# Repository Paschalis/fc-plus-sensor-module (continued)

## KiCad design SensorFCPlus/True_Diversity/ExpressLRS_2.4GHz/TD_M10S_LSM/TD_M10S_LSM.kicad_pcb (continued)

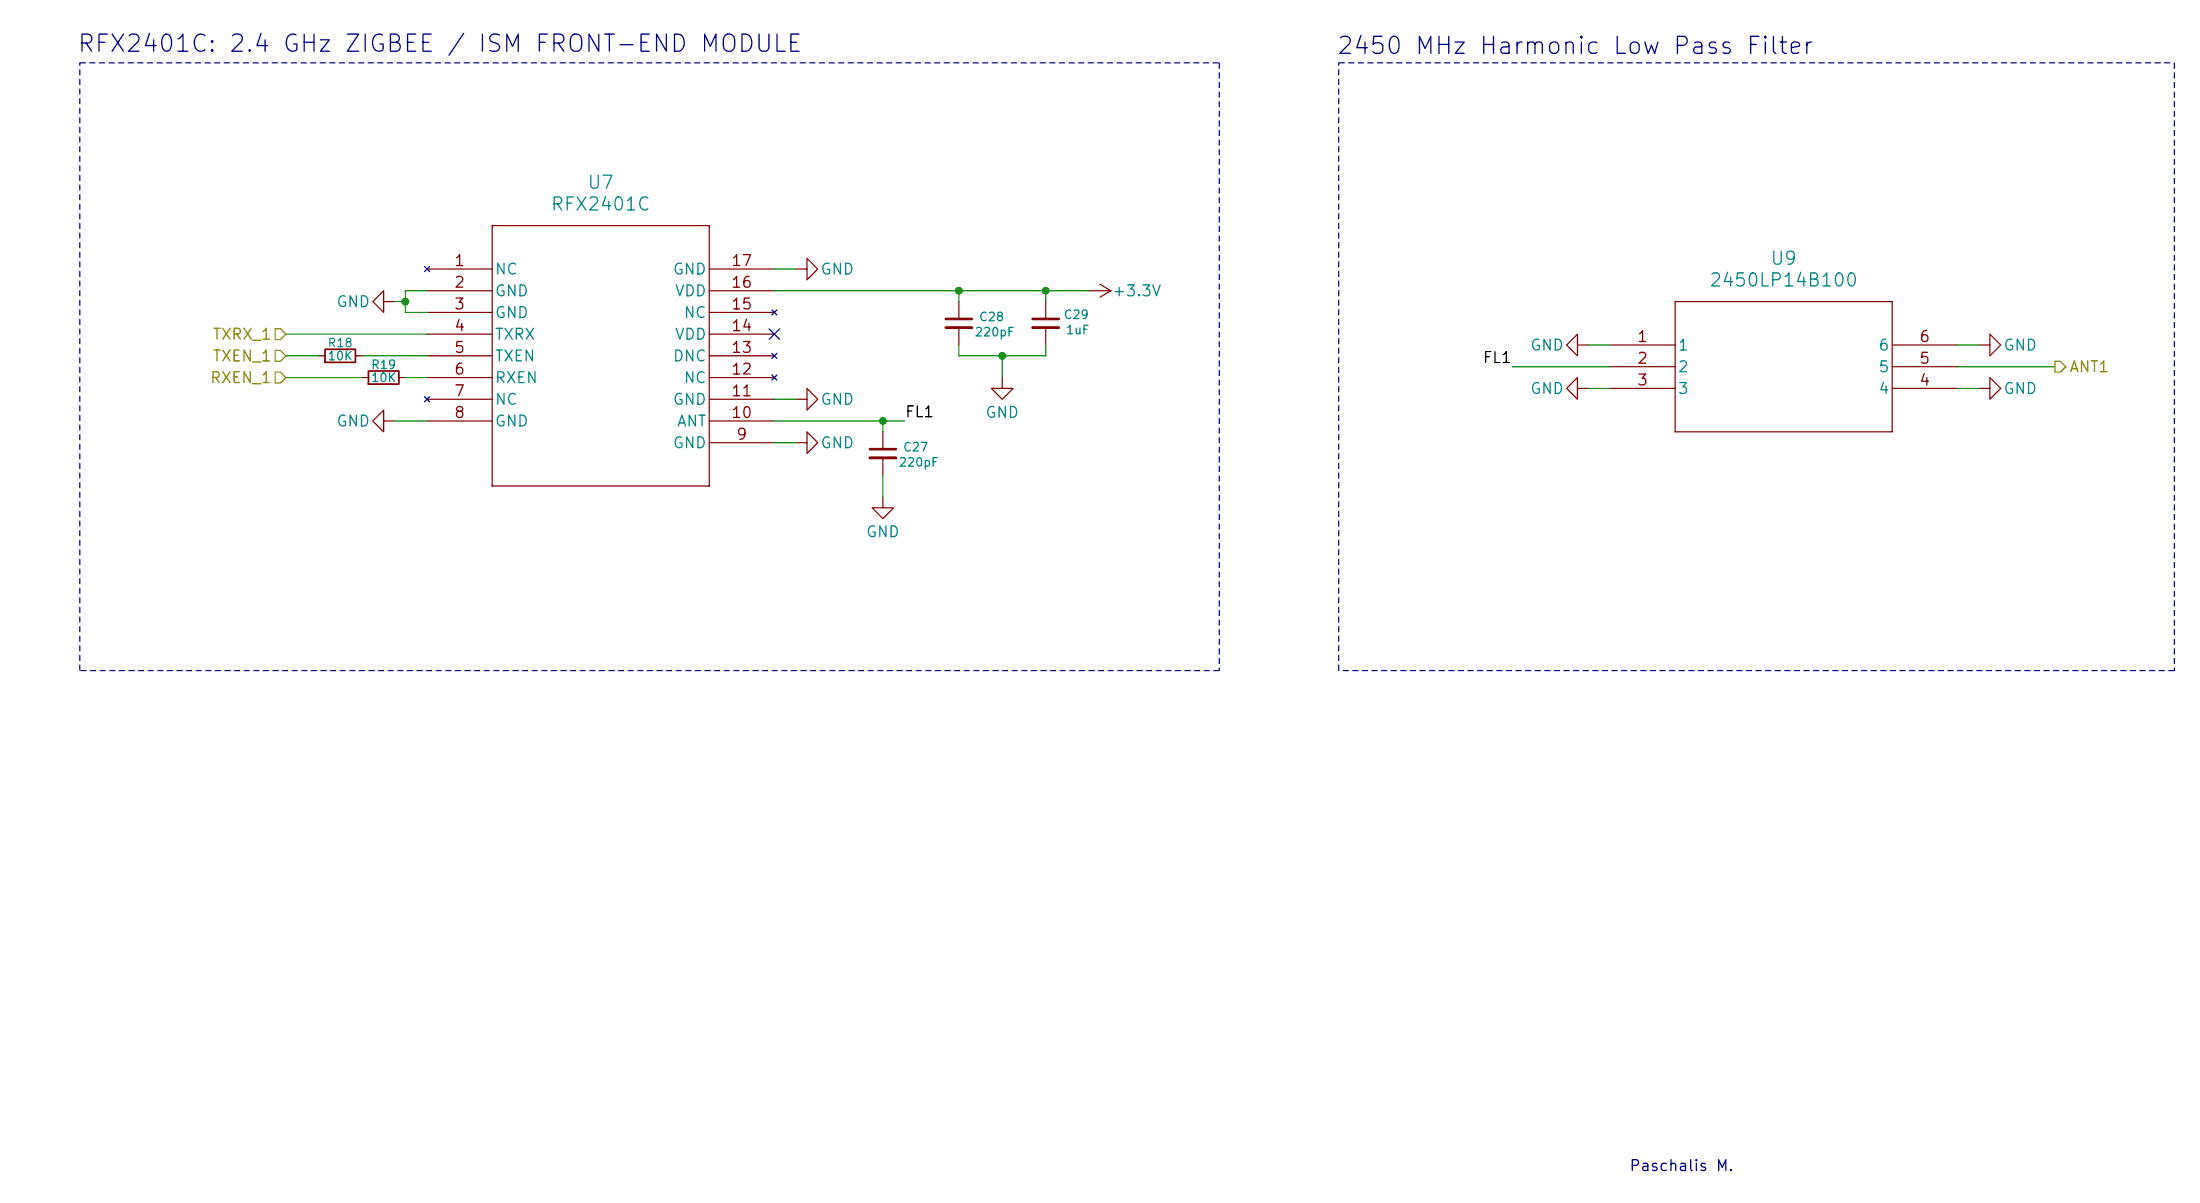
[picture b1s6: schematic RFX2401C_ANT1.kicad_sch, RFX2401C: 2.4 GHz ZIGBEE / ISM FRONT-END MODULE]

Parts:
C27, C28: 220pF; C_0603_1608Metric_Pad1.08x0.95mm_HandSolder
C29: 1uF; C_0603_1608Metric_Pad1.08x0.95mm_HandSolder
R18, R19: 10K; R_0603_1608Metric_Pad0.98x0.95mm_HandSolder
U7: RFX2401C; RFX2401C_SKY
U9: 2450LP14B100; CHIP_SMD_1P6XP8_JOD

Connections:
+3.3V: C28.1, C29.1, U7.16 (VDD); also elsewhere on the board
/ESP32/RXEN_1: R19.1; also elsewhere on the board
/ESP32/TXEN_1: R18.1; also elsewhere on the board
/RFX2401C_ANT1/ANT1: U9.5; also elsewhere on the board
/RFX2401C_ANT1/FL1: C27.1, U7.10 (ANT), U9.2
/RFX2401C_ANT1/TXRX_1: U7.4 (TXRX); also elsewhere on the board
GND: C27.2, C28.2, C29.2, U7.2 (GND), U7.3 (GND), U7.8 (GND), U7.9 (GND), U7.11 (GND), U7.17 (GND), U9.1, U9.3, U9.4, U9.6; also elsewhere on the board
unnamed: R19.2, U7.6 (RXEN)
unnamed: R18.2, U7.5 (TXEN)

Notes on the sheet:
2450 MHz Harmonic Low Pass Filter
Paschalis M.
RFX2401C: 2.4 GHz ZIGBEE / ISM FRONT-END MODULE

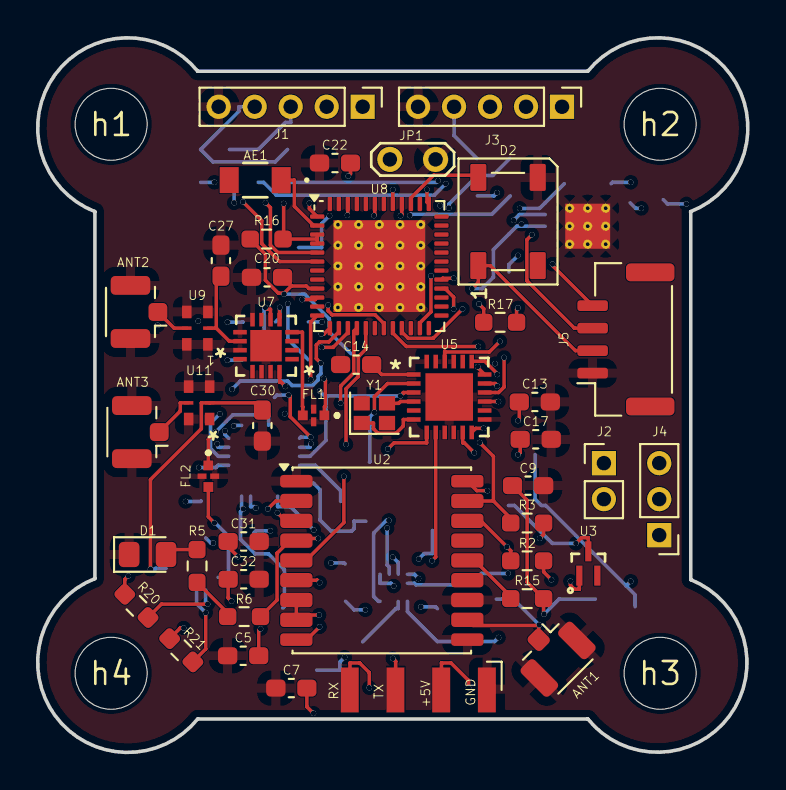
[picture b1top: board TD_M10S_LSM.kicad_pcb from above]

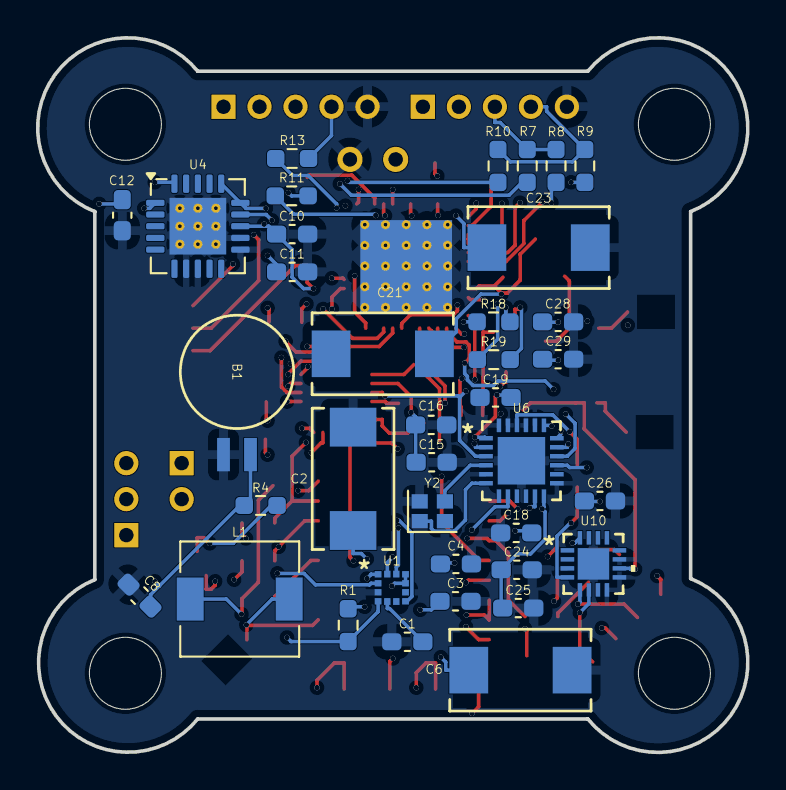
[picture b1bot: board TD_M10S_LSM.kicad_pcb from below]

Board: 4 copper layers, 39.4 x 39.7 mm, 85 parts (37 on the bottom side), 71 nets.

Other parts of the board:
h1, h2, h3, h4: MountingHole_4mm

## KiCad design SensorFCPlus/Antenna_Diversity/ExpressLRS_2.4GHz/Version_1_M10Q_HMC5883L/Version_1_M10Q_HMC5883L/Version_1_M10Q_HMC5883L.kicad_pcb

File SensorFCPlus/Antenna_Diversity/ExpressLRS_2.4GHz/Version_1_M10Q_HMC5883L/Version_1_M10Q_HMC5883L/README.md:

<div align="center">

# V1-M10Q-HMC

Antenna Diversity 
(GPS: SAM-M10Q, MAG: HMC5883L, ELRS:2.4GHz_RX)

</div>

## Bill of Materials

| Reference          | Value               | Datasheet                                                                 | Footprint                                                                                                      | Qty | DNP |
|--------------------|---------------------|---------------------------------------------------------------------------|---------------------------------------------------------------------------------------------------------------|-----|-----|
| AE1                | Antenna             | N/A                                                                       | RF_Antenna:Texas_SWRA117D_2.4GHz_Right                                                                        | 1   |     |
| ANT1, ANT2         | Conn_Coaxial        | N/A                                                                       | Connector_Coaxial:U.FL_Hirose_U.FL-R-SMT-1_Vertical                                                           | 2   |     |
| B1                 | MS621FEFL11E        | [Datasheet](MS621FEFL11E)                                                 | MS621FE-FL11E:MS621FE-FL11E                                                                                   | 1   |     |
| C1, C4, C6...      | 0.1uF               | N/A                                                                       | Capacitor_SMD:C_0805_2012Metric_Pad1.18x1.45mm_HandSolder                                                     | 6   |     |
| C2                 | 0.22uF              | N/A                                                                       | Capacitor_SMD:C_0805_2012Metric_Pad1.18x1.45mm_HandSolder                                                     | 1   |     |
| C3                 | 4.7uF               | N/A                                                                       | Capacitor_SMD:C_0805_2012Metric_Pad1.18x1.45mm_HandSolder                                                     | 1   |     |
| C5, C7, C14, C21   | 10uF                | N/A                                                                       | Capacitor_SMD:C_0805_2012Metric_Pad1.18x1.45mm_HandSolder, ECASD40J106M055K00:ECASD40J106M055K00              | 4   |     |
| C8                 | 1uF                 | N/A                                                                       | Capacitor_SMD:C_0805_2012Metric_Pad1.18x1.45mm_HandSolder                                                     | 1   |     |
| C9                 | 47uF                | N/A                                                                       | Capacitor_SMD:C_0805_2012Metric_Pad1.18x1.45mm_HandSolder                                                     | 1   |     |
| C10, C11, C16...   | 100nF               | N/A                                                                       | Capacitor_SMD:C_0805_2012Metric_Pad1.18x1.45mm_HandSolder                                                     | 10  |     |
| C22, C23, C30, C31 | 10pF                | N/A                                                                       | Capacitor_SMD:C_0805_2012Metric_Pad1.18x1.45mm_HandSolder                                                     | 4   |     |
| C25, C26           | 10nF                | N/A                                                                       | Capacitor_SMD:C_0805_2012Metric_Pad1.18x1.45mm_HandSolder                                                     | 2   |     |
| C27                | 470nF               | N/A                                                                       | Capacitor_SMD:C_0805_2012Metric_Pad1.18x1.45mm_HandSolder                                                     | 1   |     |
| C29                | 2.2uF               | N/A                                                                       | Capacitor_SMD:C_0805_2012Metric_Pad1.18x1.45mm_HandSolder                                                     | 1   |     |
| D1, D2             | LED                 | N/A                                                                       | LED_SMD:LED_0805_2012Metric_Pad1.15x1.40mm_HandSolder                                                         | 2   |     |
| FL1                | 2450FM07D0034T      | [Datasheet](https://www.mouser.co.uk/datasheet/2/611/2450FM07D0034-1375634.pdf) | 2450FM07D0034T:2450FM07D0034T                                                                                 | 1   |     |
| J1                 | Conn_01x05_Pin      | N/A                                                                       | Connector_PinHeader_2.00mm:PinHeader_1x05_P2.00mm_Vertical                                                    | 1   |     |
| J2                 | Conn_01x02_Pin      | N/A                                                                       | Connector_PinHeader_2.00mm:PinHeader_1x02_P2.00mm_Vertical                                                    | 1   |     |
| J3                 | Conn_01x03_Socket   | N/A                                                                       | Connector_JST:JST_GH_SM03B-GHS-TB_1x03-1MP_P1.25mm_Horizontal                                                 | 1   |     |
| J5                 | Conn_01x04_Pin      | N/A                                                                       | Connector_JST:JST_GH_SM04B-GHS-TB_1x04-1MP_P1.25mm_Horizontal                                                 | 1   |     |
| J6                 | Conn_01x04_Socket   | N/A                                                                       | Connector_Harwin:Harwin_M20-89004xx_1x04_P2.54mm_Horizontal                                                   | 1   |     |
| JP1                | Jumper_2_Bridged    | N/A                                                                       | Jumper:SolderJumper-2_P1.3mm_Open_RoundedPad1.0x1.5mm                                                         | 1   |     |
| R1, R2, R8, R9     | 1.5K                | N/A                                                                       | Resistor_SMD:R_0805_2012Metric_Pad1.20x1.40mm_HandSolder                                                      | 4   |     |
| R3, R6, R18...     | 0                   | N/A                                                                       | Resistor_SMD:R_0603_1608Metric_Pad0.98x0.95mm_HandSolder, Resistor_SMD:R_0805_2012Metric_Pad1.20x1.40mm_HandSolder | 8   |     |
| R4                 | 4.7K                | N/A                                                                       | Resistor_SMD:R_0805_2012Metric_Pad1.20x1.40mm_HandSolder                                                      | 1   |     |
| R5, R7             | 1K                  | N/A                                                                       | Resistor_SMD:R_0805_2012Metric_Pad1.20x1.40mm_HandSolder                                                      | 2   |     |
| R10, R11, R12...   | 10K                 | N/A                                                                       | Resistor_SMD:R_0805_2012Metric_Pad1.20x1.40mm_HandSolder                                                      | 5   |     |
| R14                | 12K                 | N/A                                                                       | Resistor_SMD:R_0805_2012Metric_Pad1.20x1.40mm_HandSolder                                                      | 1   |     |
| R15                | 2.2K                | N/A                                                                       | Resistor_SMD:R_0805_2012Metric_Pad1.20x1.40mm_HandSolder                                                      | 1   |     |
| R16                | 1.2K                | N/A                                                                       | Resistor_SMD:R_0805_2012Metric_Pad1.20x1.40mm_HandSolder                                                      | 1   |     |
| U1                 | HMC5883L            | [Datasheet](HMC5883L)                                                     | HMC5883L:LPCC16_HNW                                                                                           | 1   |     |
| U2                 | SAM-M10Q-00B        | [Datasheet](SAM-M10Q-00B)                                                 | SAM-M10Q-00B:SAM-M10Q_UBL                                                                                     | 1   |     |
| U3                 | BAT54STA            | [Datasheet](BAT54STA)                                                     | BAT54STA:BAT54STA                                                                                             | 1   |     |
| U4                 | TPS7A4701xRGW       | [Datasheet](https://www.ti.com/lit/ds/symlink/tps7a47.pdf)               | Package_DFN_QFN:Texas_RGW0020A_VQFN-20-1EP_5x5mm_P0.65mm_EP3.15x3.15mm_ThermalVias                            | 1   |     |
| U5                 | ESP8285H16          | [Datasheet](ESP8285H16)                                                   | ESP8285H16:QFN32_5X5_EXP                                                                                      | 1   |     |
| U6                 | SX1280IMLTRT       | [Datasheet](SX1280IMLTRT)                                                | SX1280IMLTRT:QFN24_4X4_SEM                                                                                    | 1   |     |
| U7                 | SE2431L-R           | [Datasheet](SE2431L-R)                                                    | SE2431L-R:SE2431L_SKY                                                                                         | 1   |     |
| Y1                 | 26MHz               | N/A                                                                       | Crystal:Crystal_SMD_2016-4Pin_2.0x1.6mm                                                                       | 1   |     |
| Y2                 | 52MHz               | N/A                                                                       | Crystal:Crystal_SMD_2016-4Pin_2.0x1.6mm                                                                       | 1   |     |

[⬅️ Go Back to Main README](https://github.com/Paschalis/fc-plus-sensor-module)

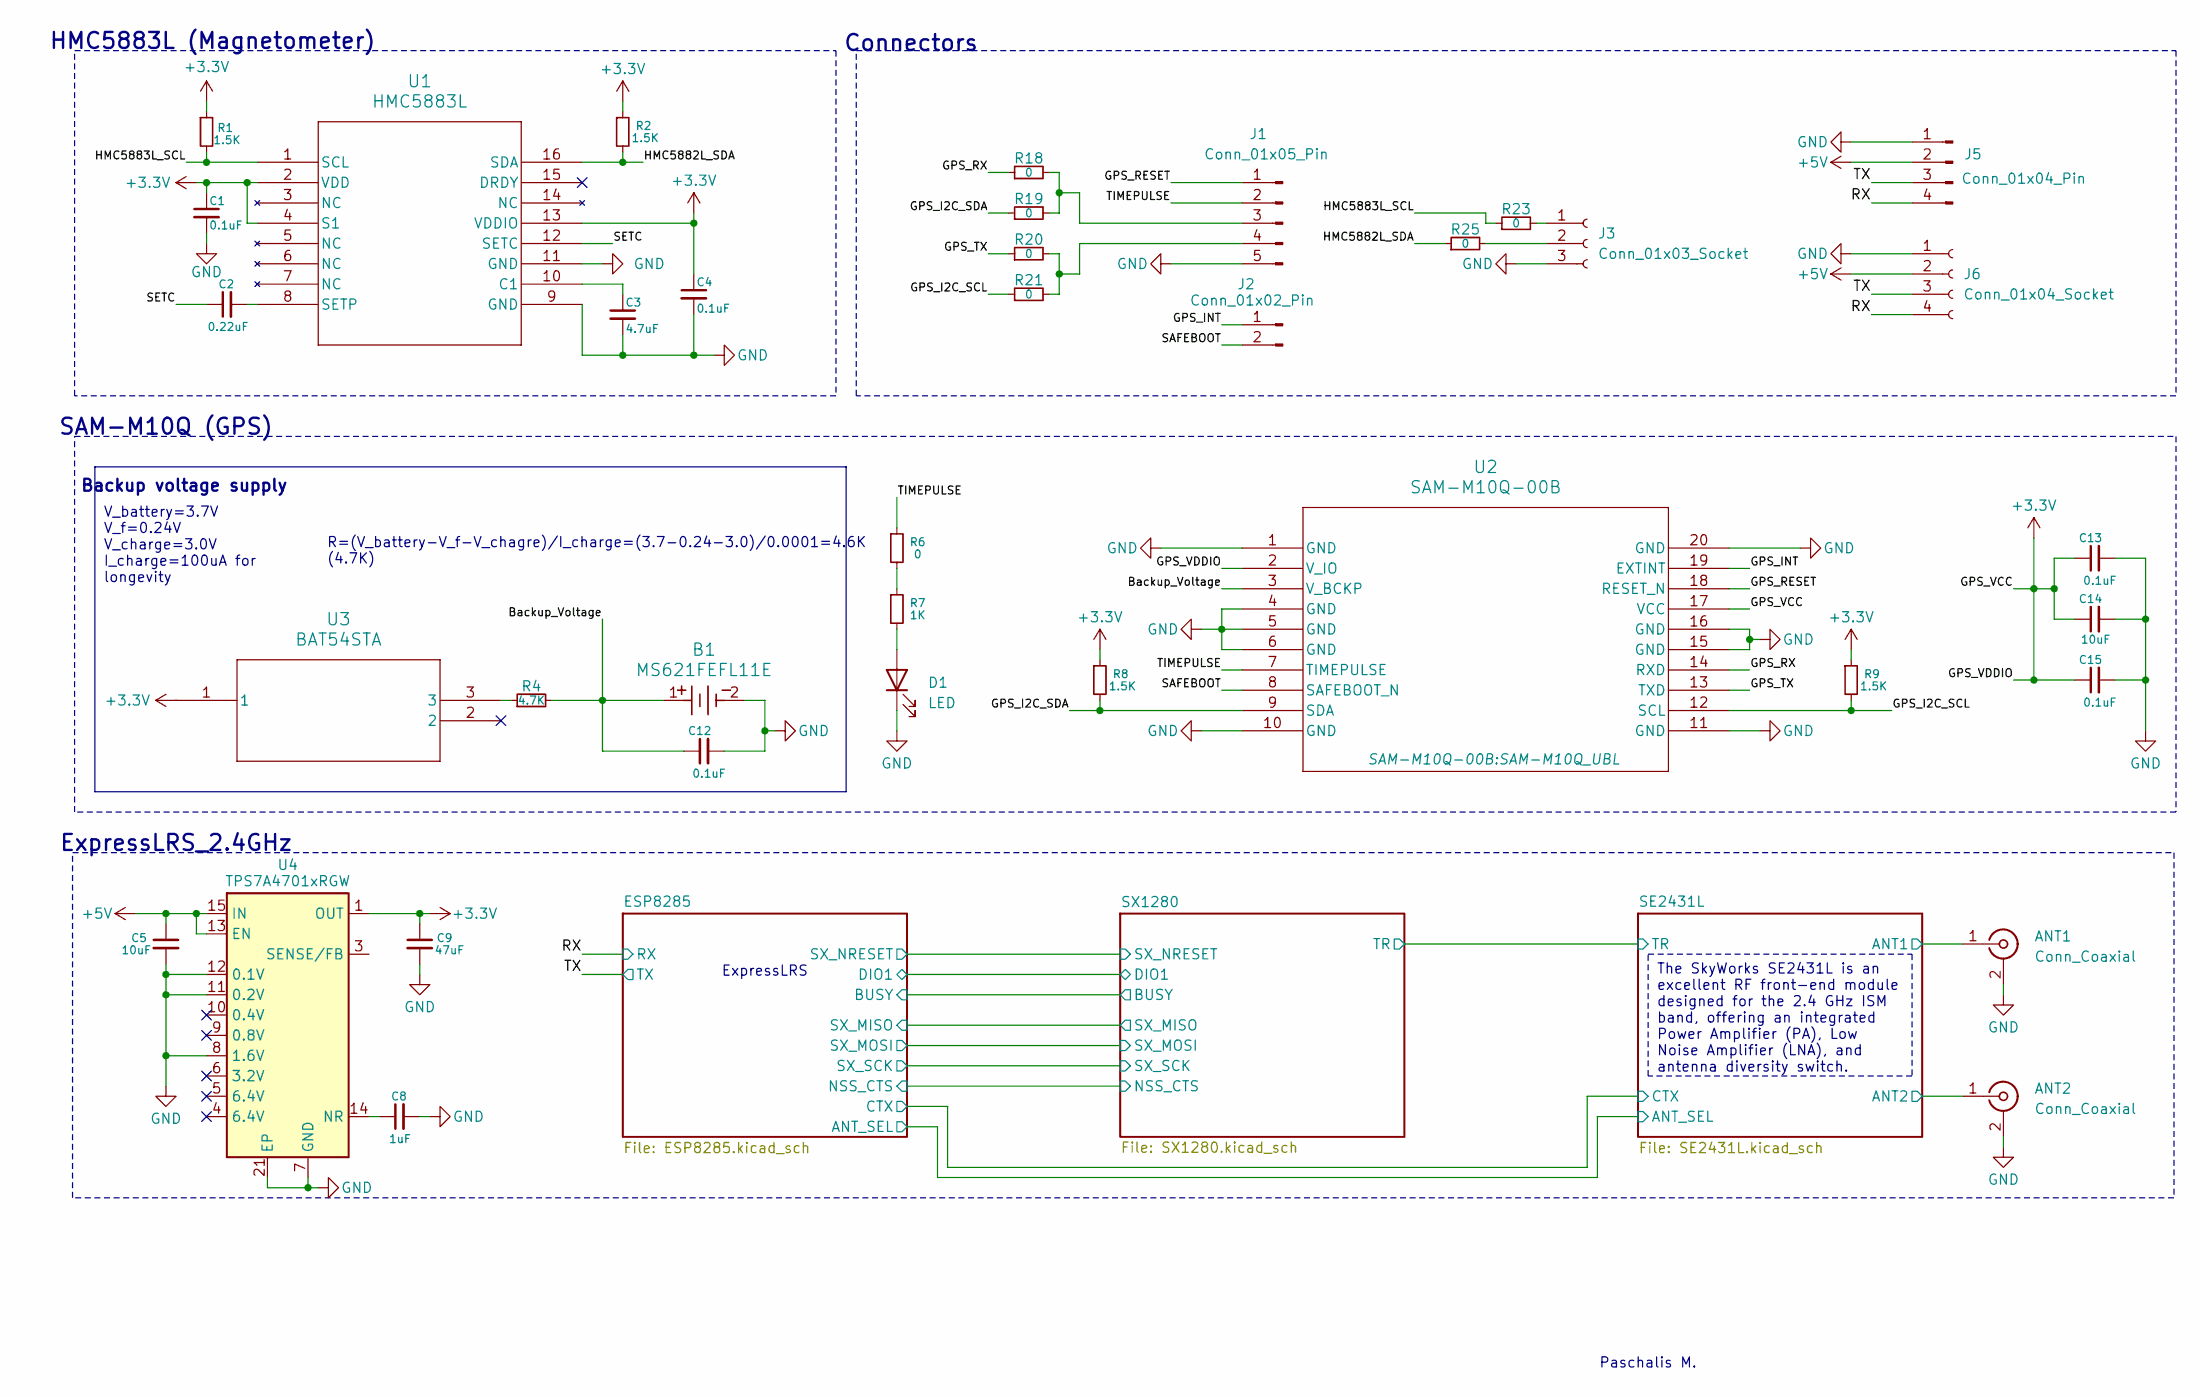
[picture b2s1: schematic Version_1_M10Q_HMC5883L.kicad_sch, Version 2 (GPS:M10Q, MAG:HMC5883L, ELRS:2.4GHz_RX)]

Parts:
ANT1, ANT2: Conn_Coaxial; U.FL_Hirose_U.FL-R-SMT-1_Vertical
B1: MS621FEFL11E; MS621FE-FL11E
C1, C4, C12, C13, C15: 0.1uF; C_0805_2012Metric_Pad1.18x1.45mm_HandSolder
C2: 0.22uF; C_0805_2012Metric_Pad1.18x1.45mm_HandSolder
C3: 4.7uF; C_0805_2012Metric_Pad1.18x1.45mm_HandSolder
C5: 10uF; C_0805_2012Metric_Pad1.18x1.45mm_HandSolder
C8: 1uF; C_0805_2012Metric_Pad1.18x1.45mm_HandSolder
C9: 47uF; C_0805_2012Metric_Pad1.18x1.45mm_HandSolder
C14: 10uF; ECASD40J106M055K00
D1: LED; LED_0805_2012Metric_Pad1.15x1.40mm_HandSolder
J1: Conn_01x05_Pin; PinHeader_1x05_P2.00mm_Vertical
J2: Conn_01x02_Pin; PinHeader_1x02_P2.00mm_Vertical
J3: Conn_01x03_Socket; JST_GH_SM03B-GHS-TB_1x03-1MP_P1.25mm_Horizontal
J5: Conn_01x04_Pin; JST_GH_SM04B-GHS-TB_1x04-1MP_P1.25mm_Horizontal
J6: Conn_01x04_Socket; Harwin_M20-89004xx_1x04_P2.54mm_Horizontal
R1, R2, R8, R9: 1.5K; R_0805_2012Metric_Pad1.20x1.40mm_HandSolder
R4: 4.7K; R_0805_2012Metric_Pad1.20x1.40mm_HandSolder
R6: 0; R_0805_2012Metric_Pad1.20x1.40mm_HandSolder
R7: 1K; R_0805_2012Metric_Pad1.20x1.40mm_HandSolder
R18, R19, R20, R21, R23, R25: 0; R_0603_1608Metric_Pad0.98x0.95mm_HandSolder
U1: HMC5883L; LPCC16_HNW
U2: SAM-M10Q-00B; SAM-M10Q_UBL
U3: BAT54STA
U4: TPS7A4701xRGW; Texas_RGW0020A_VQFN-20-1EP_5x5mm_P0.65mm_EP3.15x3.15mm_Ther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

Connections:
+3.3V: C1.1, C4.1, C9.1, C13.1, C14.1, C15.1, R1.1, R2.1, R8.1, R9.1, U1.2 (VDD), U1.4 (S1), U1.13 (VDDIO), U2.2 (V_IO), U2.17 (VCC), U3.1, U4.1 (OUT), U4.20 (OUT); also elsewhere on the board
+5V: C5.1, J5.2, J6.2, U4.13 (EN), U4.15 (IN), U4.16 (IN)
/Backup_Voltage: B1.1, C12.1, R4.2, U2.3 (V_BCKP)
/GPS_I2C_SCL: R9.2, R21.1, U2.12 (SCL)
/GPS_I2C_SDA: R8.2, R19.1, U2.9 (SDA)
/GPS_INT: J2.1, U2.19 (EXTINT)
/GPS_RESET: J1.1, U2.18 (RESET_N)
/GPS_RX: R18.1, U2.14 (RXD)
/GPS_TX: R20.1, U2.13 (TXD)
/HMC5882L_SDA: R2.2, R25.1, U1.16 (SDA)
/HMC5883L_SCL: R1.2, R23.1, U1.1 (SCL)
/RX: J5.4, J6.4; also elsewhere on the board
/SAFEBOOT: J2.2, U2.8 (SAFEBOOT_N)
/SE2431L/ANT1: ANT1.1 (In); also elsewhere on the board
/SE2431L/ANT2: ANT2.1 (In); also elsewhere on the board
/SETC: C2.1, U1.12 (SETC)
/TIMEPULSE: J1.2, R6.1, U2.7 (TIMEPULSE)
/TX: J5.3, J6.3; also elsewhere on the board
GND: ANT1.2 (Ext), ANT2.2 (Ext), B1.2, C1.2, C3.2, C4.2, C5.2, C8.2, C9.2, C12.2, C13.2, C14.2, C15.2, D1.1 (K), J1.5, J3.3, J5.1, J6.1, U1.9 (GND), U1.11 (GND), U2.1 (GND), U2.4 (GND), U2.5 (GND), U2.6 (GND), U2.10 (GND), U2.11 (GND), U2.15 (GND), U2.16 (GND), U2.20 (GND), U4.7 (GND), U4.8 (1.6V), U4.11 (0.2V), U4.12 (0.1V), U4.21 (EP); also elsewhere on the board
unnamed: D1.2 (A), R7.2
unnamed: J1.3, R18.2, R19.2
unnamed: J1.4, R20.2, R21.2
unnamed: J3.1, R23.2
unnamed: J3.2, R25.2
unnamed: R4.1, U3.3
unnamed: R6.2, R7.1
unnamed: C3.1, U1.10 (C1)
unnamed: C2.2, U1.8 (SETP)
unnamed: C8.1, U4.14 (NR)

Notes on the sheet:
The SkyWorks SE2431L is an excellent RF front-end module designed for the 2.4 GHz ISM band, offering an integrated Power Amplifier (PA), Low Noise Amplifier (LNA), and antenna diversity switch.
R=(V_battery-V_f-V_chagre)/I_charge=(3.7-0.24-3.0)/0.0001=4.6K (4.7K)
V_battery=3.7V V_f=0.24V V_charge=3.0V I_charge=100uA for longevity
HMC5883L (Magnetometer)
ExpressLRS
Connectors
ExpressLRS_2.4GHz
Backup voltage supply
SAM-M10Q (GPS)
Paschalis M.

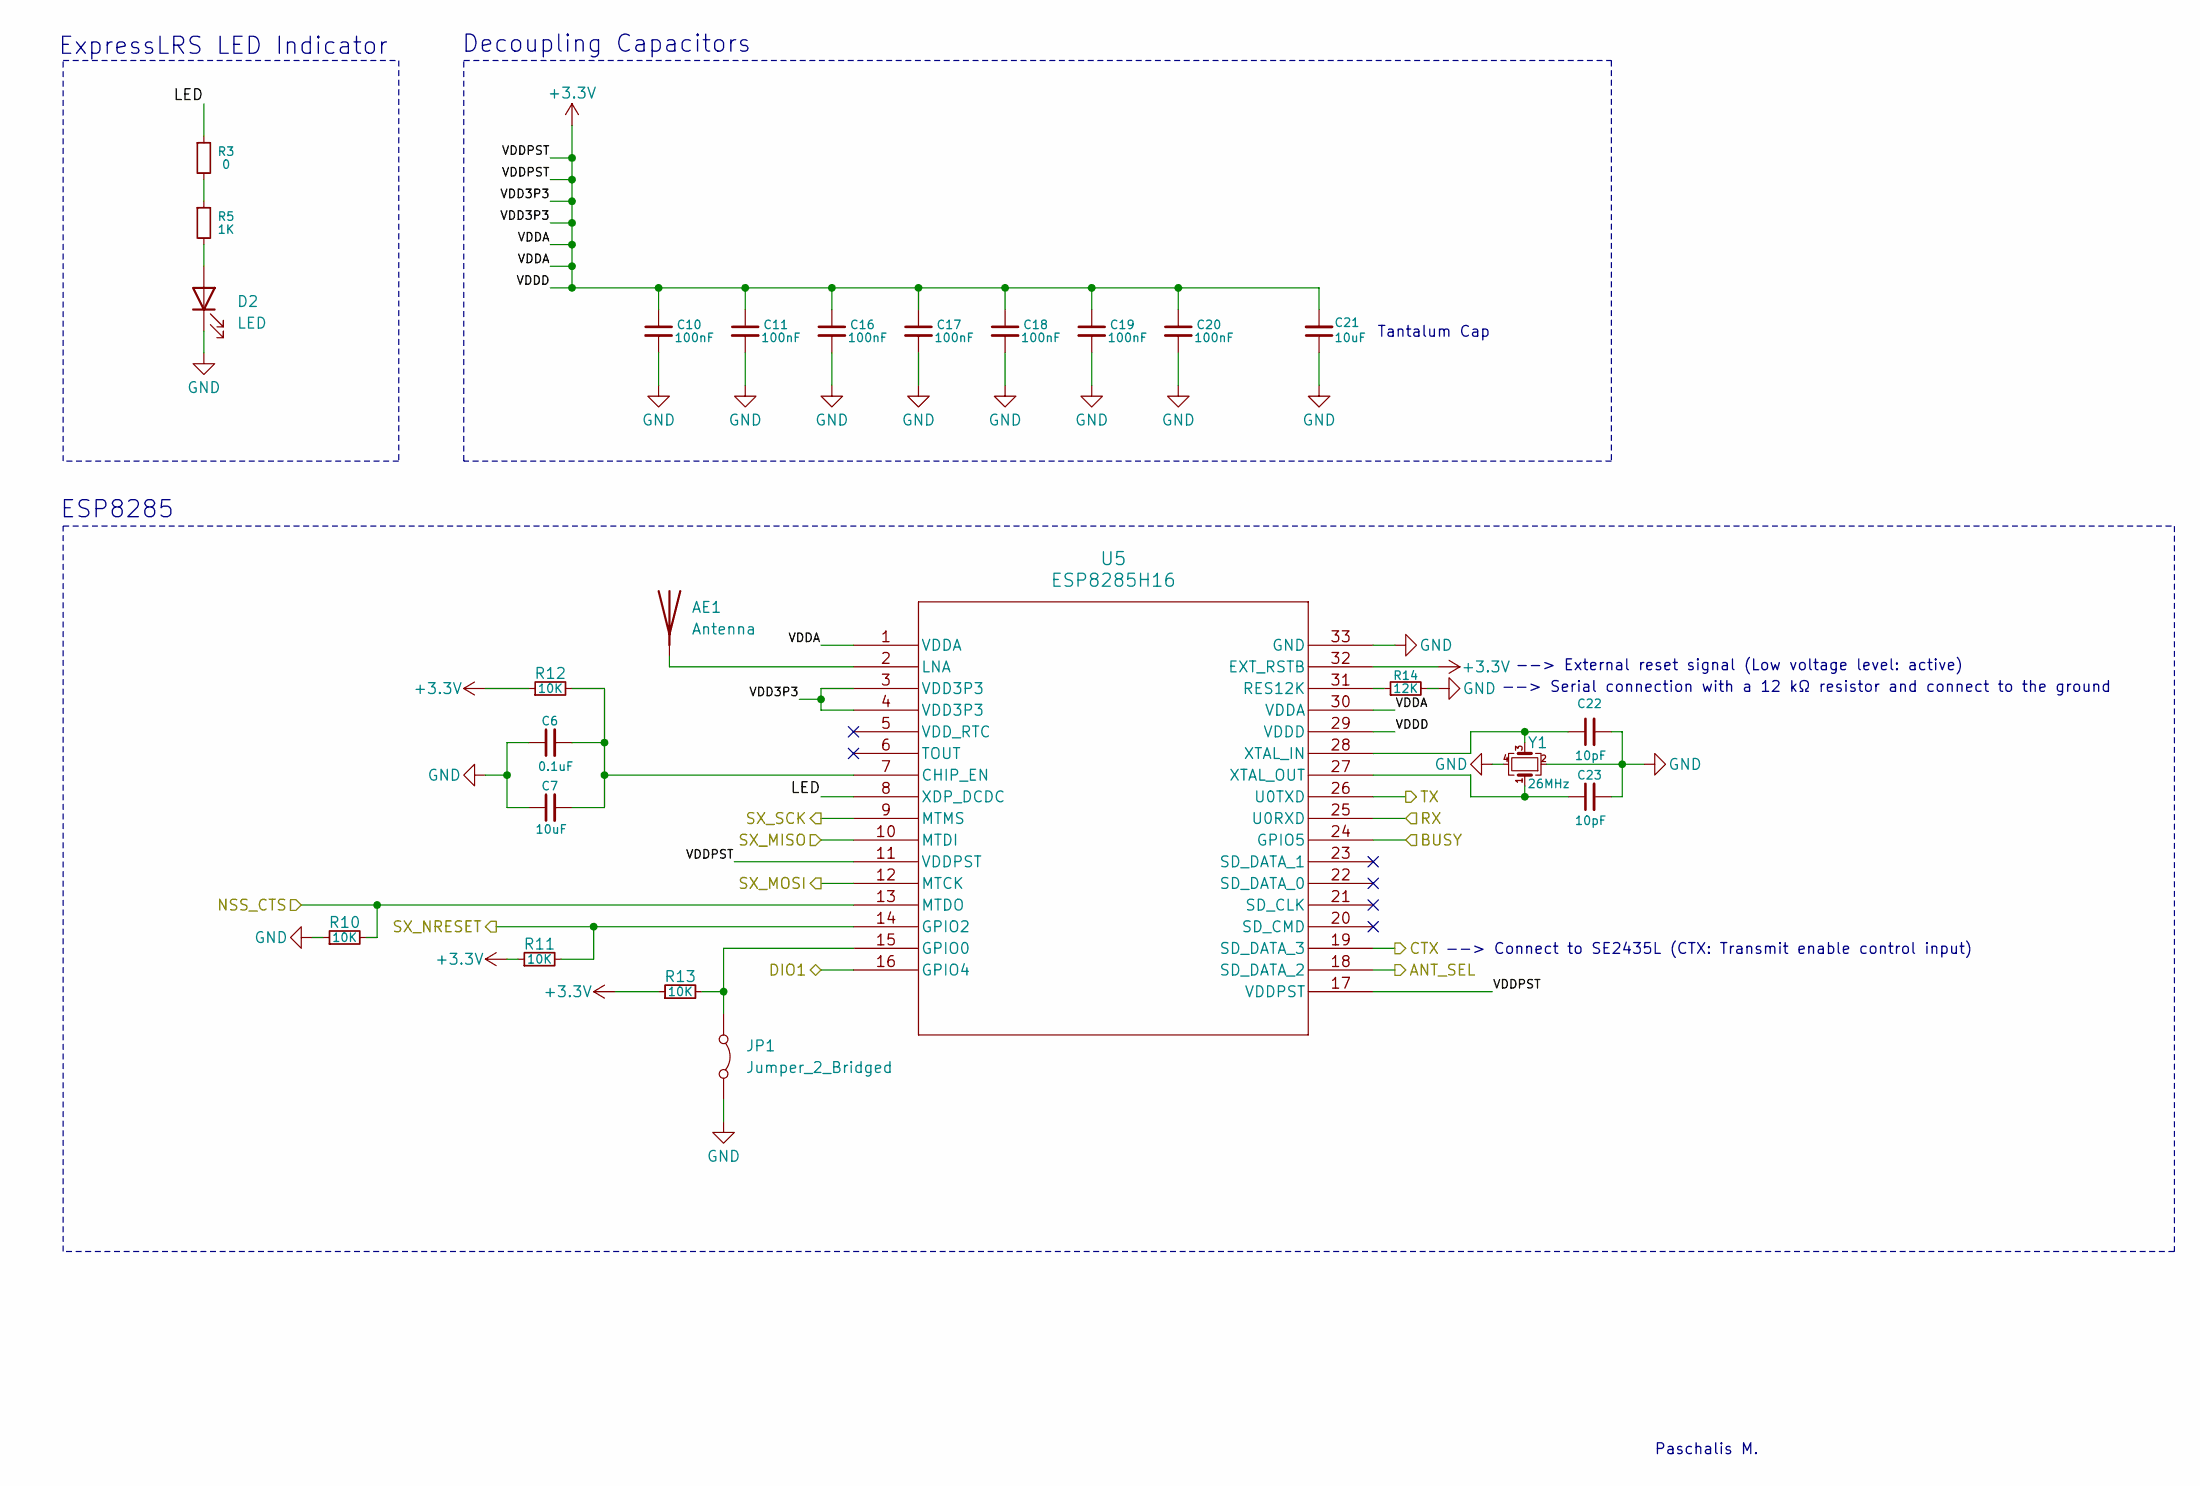
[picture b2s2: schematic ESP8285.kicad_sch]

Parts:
AE1: Antenna; Texas_SWRA117D_2.4GHz_Right
C6: 0.1uF; C_0805_2012Metric_Pad1.18x1.45mm_HandSolder
C7, C21: 10uF; ECASD40J106M055K00
C10, C11, C16, C17, C18, C19, C20: 100nF; C_0805_2012Metric_Pad1.18x1.45mm_HandSolder
C22, C23: 10pF; C_0805_2012Metric_Pad1.18x1.45mm_HandSolder
D2: LED; LED_0805_2012Metric_Pad1.15x1.40mm_HandSolder
JP1: Jumper_2_Bridged; SolderJumper-2_P1.3mm_Open_RoundedPad1.0x1.5mm
R3: 0; R_0805_2012Metric_Pad1.20x1.40mm_HandSolder
R5: 1K; R_0805_2012Metric_Pad1.20x1.40mm_HandSolder
R10, R11, R12, R13: 10K; R_0805_2012Metric_Pad1.20x1.40mm_HandSolder
R14: 12K; R_0805_2012Metric_Pad1.20x1.40mm_HandSolder
U5: ESP8285H16; QFN32_5X5_EXP
Y1: 26MHz; Crystal_SMD_2016-4Pin_2.0x1.6mm

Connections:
+3.3V: C10.1, C11.1, C16.1, C17.1, C18.1, C19.1, C20.1, C21.2, R11.1, R12.1, R13.1, U5.1 (VDDA), U5.3 (VDD3P3), U5.4 (VDD3P3), U5.11 (VDDPST), U5.17 (VDDPST), U5.29 (VDDD), U5.30 (VDDA), U5.32 (EXT_RSTB); also elsewhere on the board
/ESP8285/ANT_SEL: U5.18 (SD_DATA_2); also elsewhere on the board
/ESP8285/BUSY: U5.24 (GPIO5); also elsewhere on the board
/ESP8285/CTX: U5.19 (SD_DATA_3); also elsewhere on the board
/ESP8285/DIO1: U5.16 (GPIO4); also elsewhere on the board
/ESP8285/LED: R3.1, U5.8 (XDP_DCDC)
/ESP8285/NSS_CTS: R10.2, U5.13 (MTDO); also elsewhere on the board
/ESP8285/SX_MISO: U5.10 (MTDI); also elsewhere on the board
/ESP8285/SX_MOSI: U5.12 (MTCK); also elsewhere on the board
/ESP8285/SX_NRESET: R11.2, U5.14 (GPIO2); also elsewhere on the board
/ESP8285/SX_SCK: U5.9 (MTMS); also elsewhere on the board
/RX: U5.25 (U0RXD); also elsewhere on the board
/TX: U5.26 (U0TXD); also elsewhere on the board
GND: C6.1, C7.1, C10.2, C11.2, C16.2, C17.2, C18.2, C19.2, C20.2, C21.1, C22.2, C23.2, D2.1 (K), JP1.2 (B), R10.1, R14.2, U5.33 (GND), Y1.2, Y1.4; also elsewhere on the board
unnamed: AE1.1, U5.2 (LNA)
unnamed: D2.2 (A), R5.2
unnamed: JP1.1 (A), R13.2, U5.15 (GPIO0)
unnamed: R3.2, R5.1
unnamed: C6.2, C7.2, R12.2, U5.7 (CHIP_EN)
unnamed: R14.1, U5.31 (RES12K)
unnamed: C22.1, U5.28 (XTAL_IN), Y1.3
unnamed: C23.1, U5.27 (XTAL_OUT), Y1.1

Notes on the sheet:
ESP8285
Paschalis M.
Decoupling Capacitors
--> Serial connection with a 12 kΩ resistor and connect to the ground
--> Connect to SE2435L (CTX: Transmit enable control input)
--> External reset signal (Low voltage level: active)
ExpressLRS LED Indicator
Tantalum Cap

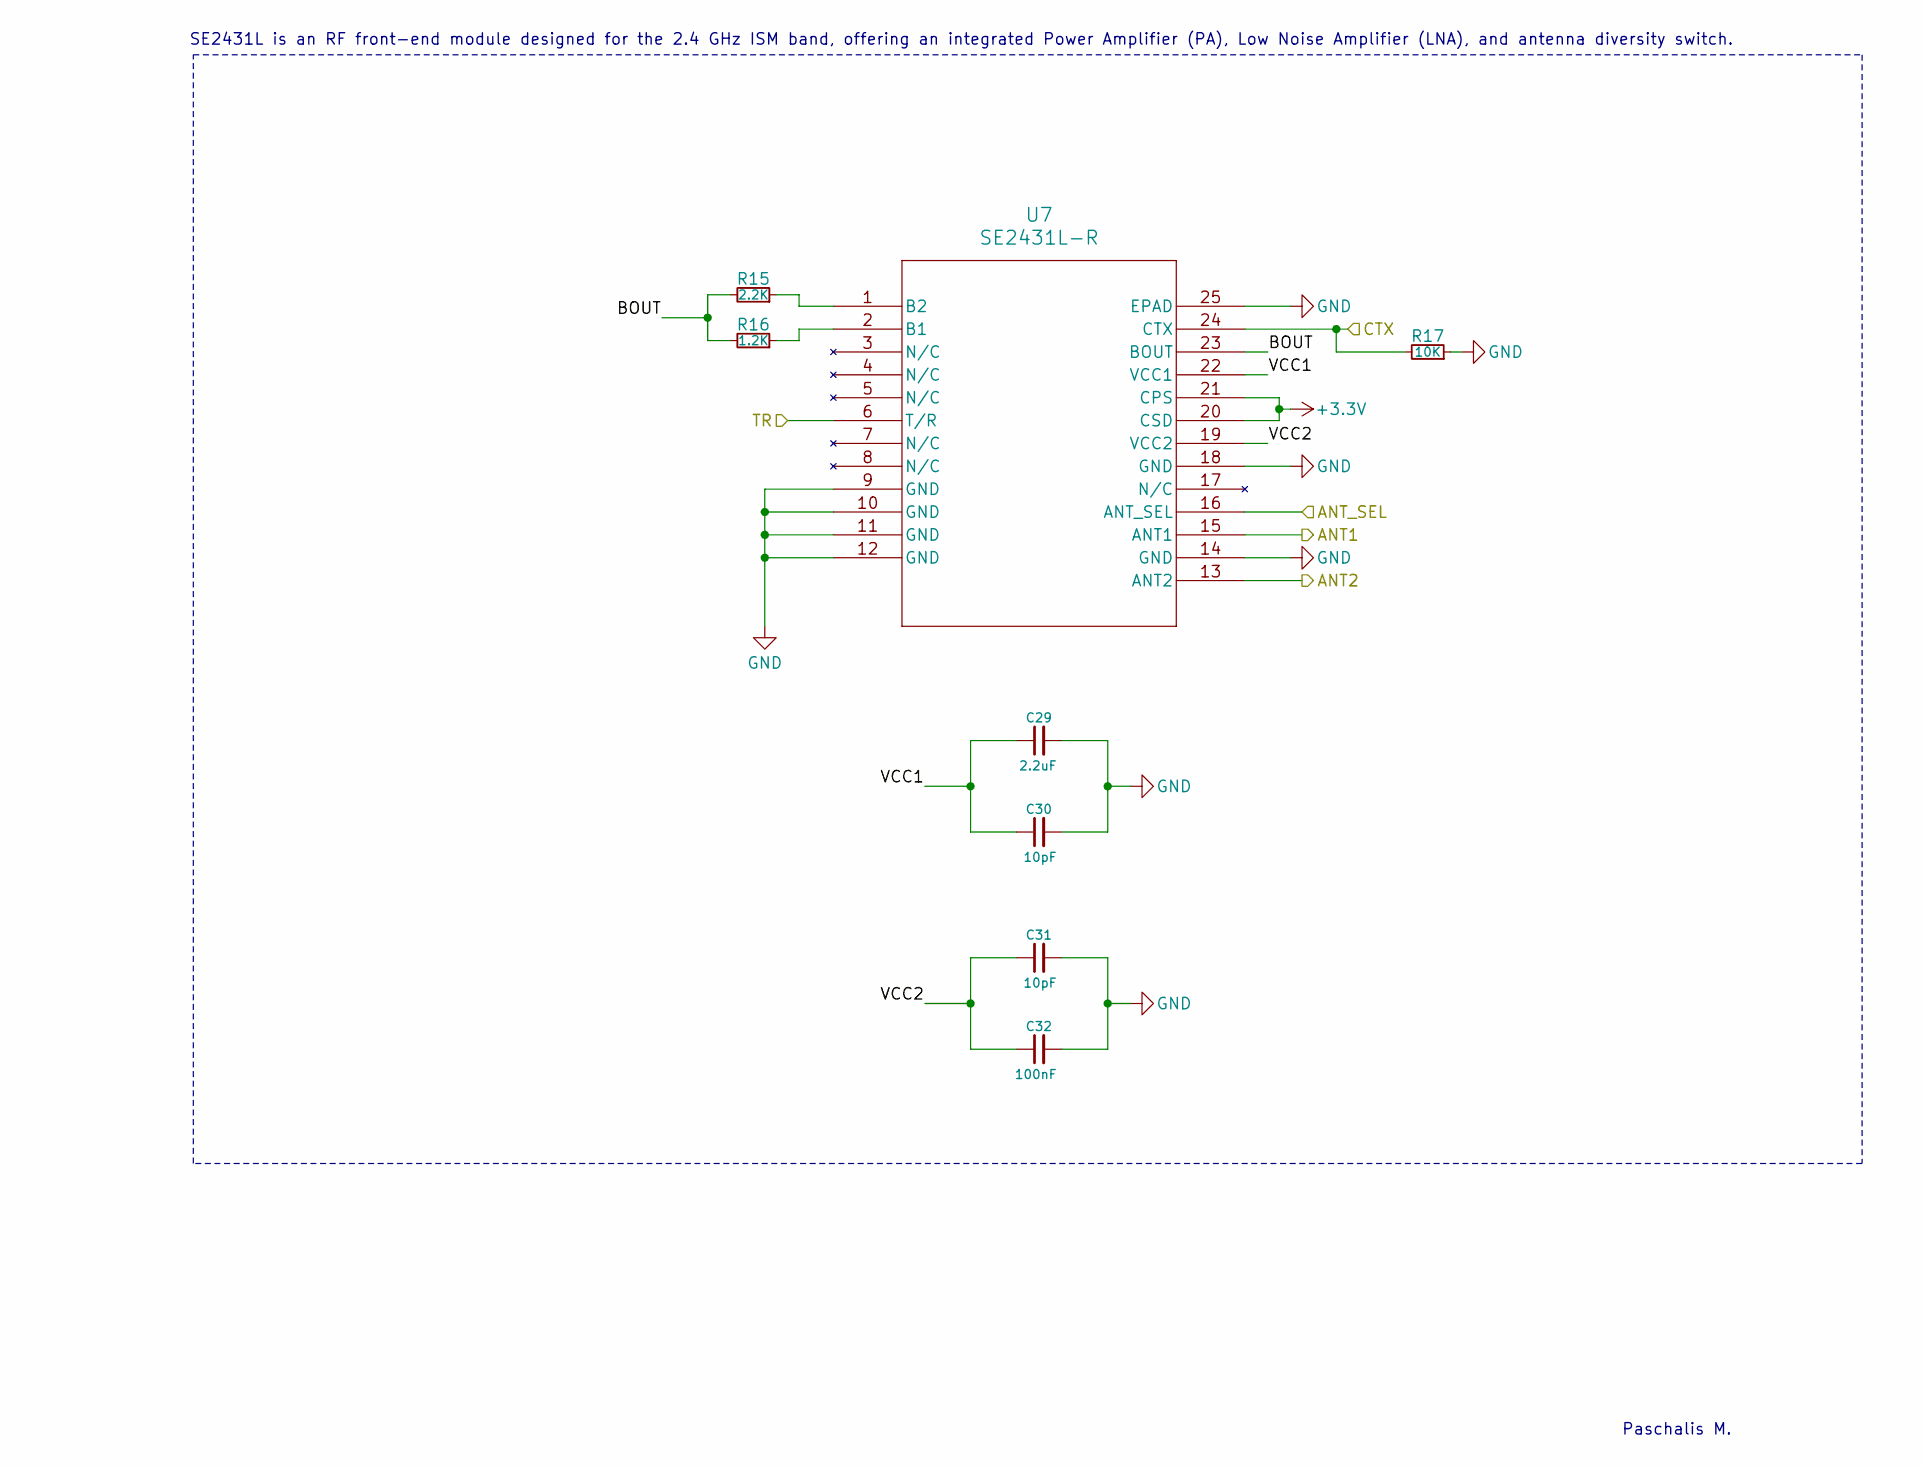
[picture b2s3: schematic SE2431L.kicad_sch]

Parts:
C29: 2.2uF; C_0805_2012Metric_Pad1.18x1.45mm_HandSolder
C30, C31: 10pF; C_0805_2012Metric_Pad1.18x1.45mm_HandSolder
C32: 100nF; C_0805_2012Metric_Pad1.18x1.45mm_HandSolder
R15: 2.2K; R_0805_2012Metric_Pad1.20x1.40mm_HandSolder
R16: 1.2K; R_0805_2012Metric_Pad1.20x1.40mm_HandSolder
R17: 10K; R_0805_2012Metric_Pad1.20x1.40mm_HandSolder
U7: SE2431L-R; SE2431L_SKY

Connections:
+3.3V: U7.20 (CSD), U7.21 (CPS); also elsewhere on the board
/ESP8285/ANT_SEL: U7.16 (ANT_SEL); also elsewhere on the board
/ESP8285/CTX: R17.2, U7.24 (CTX); also elsewhere on the board
/SE2431L/ANT1: U7.15 (ANT1); also elsewhere on the board
/SE2431L/ANT2: U7.13 (ANT2); also elsewhere on the board
/SE2431L/BOUT: R15.2, R16.2, U7.23 (BOUT)
/SE2431L/TR: U7.6 (T/R); also elsewhere on the board
/SE2431L/VCC1: C29.1, C30.1, U7.22 (VCC1)
/SE2431L/VCC2: C31.1, C32.1, U7.19 (VCC2)
GND: C29.2, C30.2, C31.2, C32.2, R17.1, U7.9 (GND), U7.10 (GND), U7.11 (GND), U7.12 (GND), U7.14 (GND), U7.18 (GND), U7.25 (EPAD); also elsewhere on the board
unnamed: R16.1, U7.2 (B1)
unnamed: R15.1, U7.1 (B2)

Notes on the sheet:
SE2431L is an RF front-end module designed for the 2.4 GHz ISM band, offering an integrated Power Amplifier (PA), Low Noise Amplifier (LNA), and antenna diversity switch.
Paschalis M.
